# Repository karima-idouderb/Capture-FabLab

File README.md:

# Capture FabLab Project

## Authors
- [BELABDELLI Rizlène](https://github.com/Riizlene)
- [BOUGHERARA Hanane](https://github.com/hanane-bougherara)
- [IDOUDERB Karima](https://github.com/karima-idouderb)
- [OUERFILI Chaïma](https://github.com/Chaimaaaaaaaaaaa)

## Overview
The Capture FabLab project was designed to address a crucial need within the FabLab: project documentation. Often overlooked or considered tedious by users, the documentation process has been simplified through a system that captures videos of the work being done and automatically uploads them to a dedicated server. This project aims to make documentation more accessible and attractive, encouraging comprehensive and regular recording throughout a project's lifecycle. This will facilitate the continuation, improvement, reproduction, and collaboration on projects within the FabLab community.

## Table of Contents
1. [Introduction](#introduction)
2. [Client Requirements](#client-requirements)
3. [System Architecture](#system-architecture)
4. [Project Development Stages](#project-development-stages)
5. [Project Validation](#project-validation)
6. [Conclusion](#conclusion)

## Introduction
The Capture FabLab project was initiated to meet a critical need in the FabLab: project documentation. Users often neglect or find this step tedious. To streamline this process, we developed a system that captures videos of ongoing work and automatically sends them to a dedicated server. The primary goal is to make documentation more accessible and appealing, thereby encouraging users to document their projects comprehensively and consistently throughout their development. This initiative aims to facilitate the continuation, improvement, reproduction, and collaboration on projects within the FabLab.

## Client Requirements
- **Video Recording Control**: Ability to start and stop video recording on demand.
- **User-friendly Interface**: Simple interface with easily identifiable buttons for starting and stopping video recording, ensuring intuitive use.
- **Battery Power**: The system must be powered by a rechargeable battery with a minimum autonomy of 6 hours and a maximum recharge time of 8 hours.
- **Recording Indicator**: An LED should clearly indicate when video recording is in progress.
- **Framerate Adjustment**: A dial to adjust the video framerate, providing flexibility in recording quality.
- **Video Storage on Dedicated Server**: Set up a server to store captured videos, ensuring data preservation and availability for FabLab users.
- **Automatic Data Transfer**: Videos should be automatically transferred from the Raspberry Pi 4 (or other components) to the server upon recording, ensuring continuous documentation.
- **Ease of Assembly for Makers**: The system should be easy to assemble and reproduce, encouraging wider adoption within the FabLab community.
- **Portable and Practical Prototype**: The prototype should be compact and lightweight for easy relocation and use in different FabLab contexts.

## System Architecture
- **Raspberry Pi 4**: Acts as the system's brain, running Python code to control video capture, manage webcam settings, handle recording, and manage video transfers to the server.
- **Webcam**: Used to capture videos of FabLab projects, connected to the Raspberry Pi 4 and controlled by the Python code.
- **External Battery**: Provides continuous power for a minimum of 6 hours as required by the client.
- **PCB (Printed Circuit Board)**: Connects and organizes electronic components, ensuring a compact layout and stable connections.
- **Enclosure**: A specially designed box houses and protects all system components, robust enough for FabLab environments while being compact for easy transport.

## Project Development Stages
1. **Research and Integration of Video Recording Code**: We began by researching and testing Python codes to capture videos from a webcam and store them on the Raspberry Pi 4. Once a functional code was found, it was modified to integrate into the system, ensuring basic recording functionality.
2. **Integration of Control Buttons**: Physical buttons were added to the system to start and stop video recording. These buttons were connected to the Raspberry Pi 4 and programmed to trigger the appropriate actions in the Python code.
3. **Framerate Selection Using a Strip Switch**: A strip switch was used to allow users to select different predefined framerate values for the video, as the Raspberry Pi 4 can only handle numerical values for framerate. This approach was chosen over a potentiometer to avoid additional analog-to-digital conversion.
4. **Testing and Adjustments**: After integrating the main functionalities, tests were conducted to ensure everything worked correctly. Adjustments were made to the code and hardware based on test results to ensure system reliability.
5. **Enclosure Design**: During development, the enclosure design was finalized to house all components neatly.

## Project Validation
- **Regular Client Meetings**: Bi-weekly meetings with the client were held to discuss project progress, gather feedback on developed features, and obtain advice and recommendations. These meetings ensured transparent and effective communication, ensuring the project met the client's needs.
- **Regular Testing**: Continuous testing was performed throughout development to verify that all system functionalities worked correctly, including video recording, control buttons, framerate selection, etc.
- **Internal Team Meetings**: Regular team meetings were held to organize tasks, discuss challenges, and resolve any obstacles. These meetings ensured effective collaboration and smooth project progress.

## Conclusion
The Capture FabLab project has been successful on many fronts. Not only did we deliver a functional and reliable prototype on time, but we also gained valuable skills and experiences for future projects. Despite the challenges encountered, our determination and commitment were key to our success. This project represents an important milestone in our professional journey, and we are proud of the contribution we have made to the FabLab community.

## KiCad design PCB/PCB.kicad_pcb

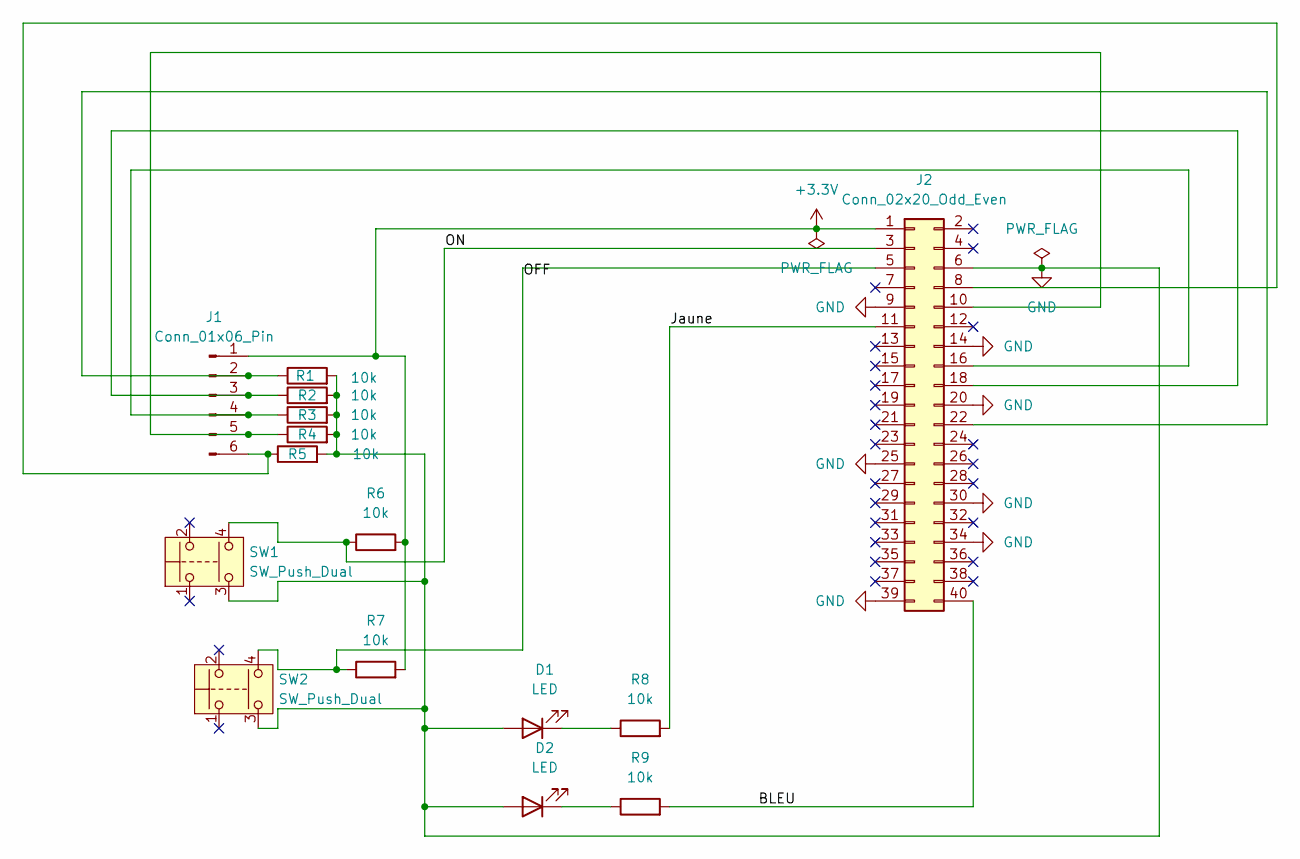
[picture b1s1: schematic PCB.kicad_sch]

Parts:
D1, D2: LED; LED_D5.0mm
J1: Conn_01x06_Pin; PinSocket_1x06_P2.54mm_Vertical
J2: Conn_02x20_Odd_Even; PinSocket_2x20_P2.54mm_Vertical
R1, R2, R3, R4, R5, R6, R7, R8, R9: 10k; R_Axial_DIN0207_L6.3mm_D2.5mm_P10.16mm_Horizontal
SW1, SW2: SW_Push_Dual; Push_E-Switch_KS01Q01

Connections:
+3.3V: J1.1, J2.1, R6.2, R7.2
/BLEU: J2.40, R9.2
/Jaune: J2.11, R8.2
/OFF: J2.5, R7.1, SW2.4
/ON: J2.3, R6.1, SW1.4
GND: D1.2 (A), D2.2 (A), J2.6, J2.9, J2.14, J2.20, J2.25, J2.30, J2.34, J2.39, R1.2, R2.2, R3.2, R4.2, R5.2, SW1.3, SW2.3
unnamed: D1.1 (K), R8.1
unnamed: D2.1 (K), R9.1
unnamed: J1.2, J2.22, R1.1
unnamed: J1.3, J2.18, R2.1
unnamed: J1.4, J2.16, R3.1
unnamed: J1.5, J2.10, R4.1
unnamed: J1.6, J2.8, R5.1

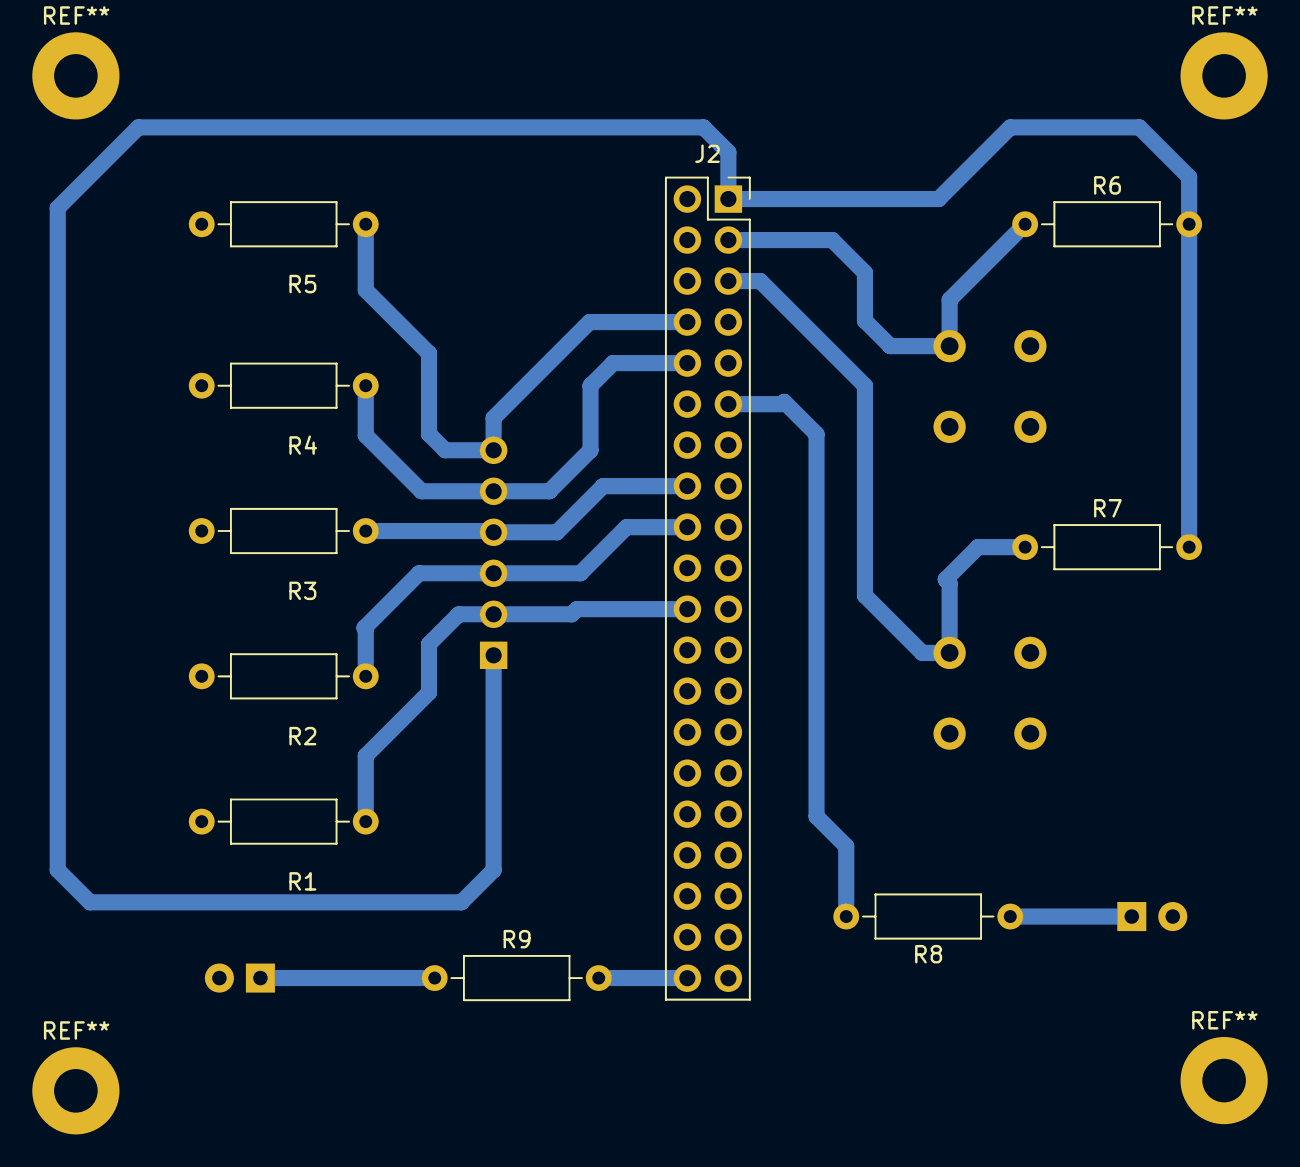
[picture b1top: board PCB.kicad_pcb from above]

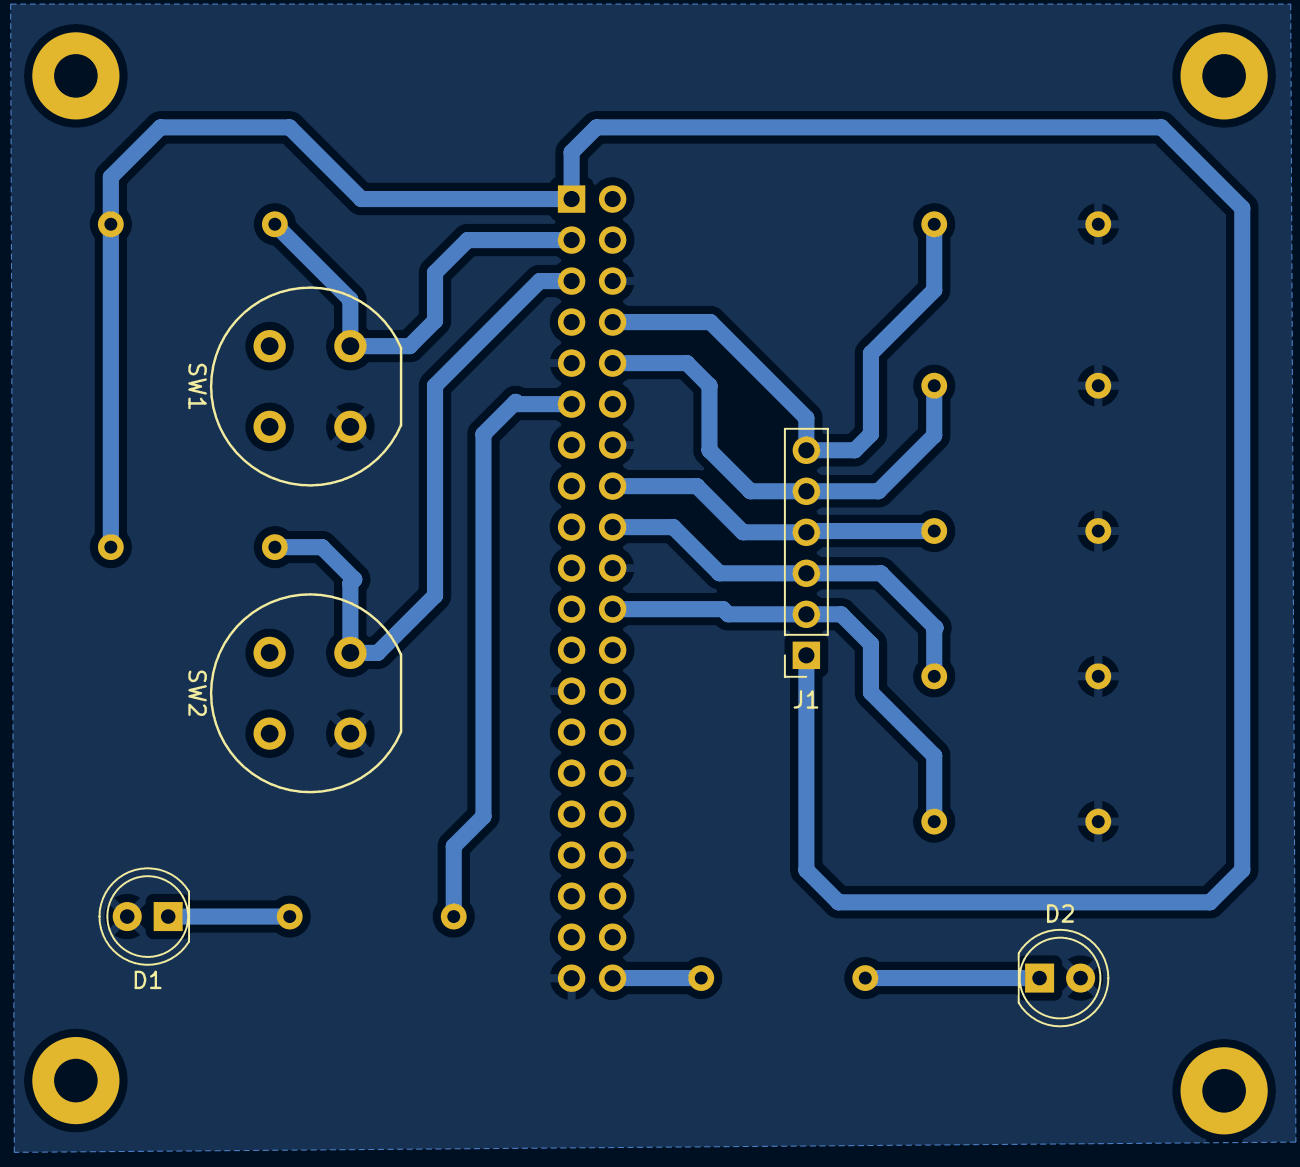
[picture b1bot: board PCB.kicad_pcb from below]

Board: 2 copper layers, 15 parts (5 on the bottom side), 13 nets.

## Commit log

2024-05-19 Commentaire final.py
